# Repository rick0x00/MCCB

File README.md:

# MCCB
MODULO DE CONTROLE DE CARRINHO DE BRINQUEDO

## Warning
I, the project maintainer ,am a beginner in this Open Source world, Git, GitHub... So I apologize in advance for any problems.

## License
At the present time this project is completely under [Apache 2.0 license](http://www.apache.org/licenses/LICENSE-2.0). All Softwares, All Electronic Designs(Schematics), All Documentation and All 3D Design.

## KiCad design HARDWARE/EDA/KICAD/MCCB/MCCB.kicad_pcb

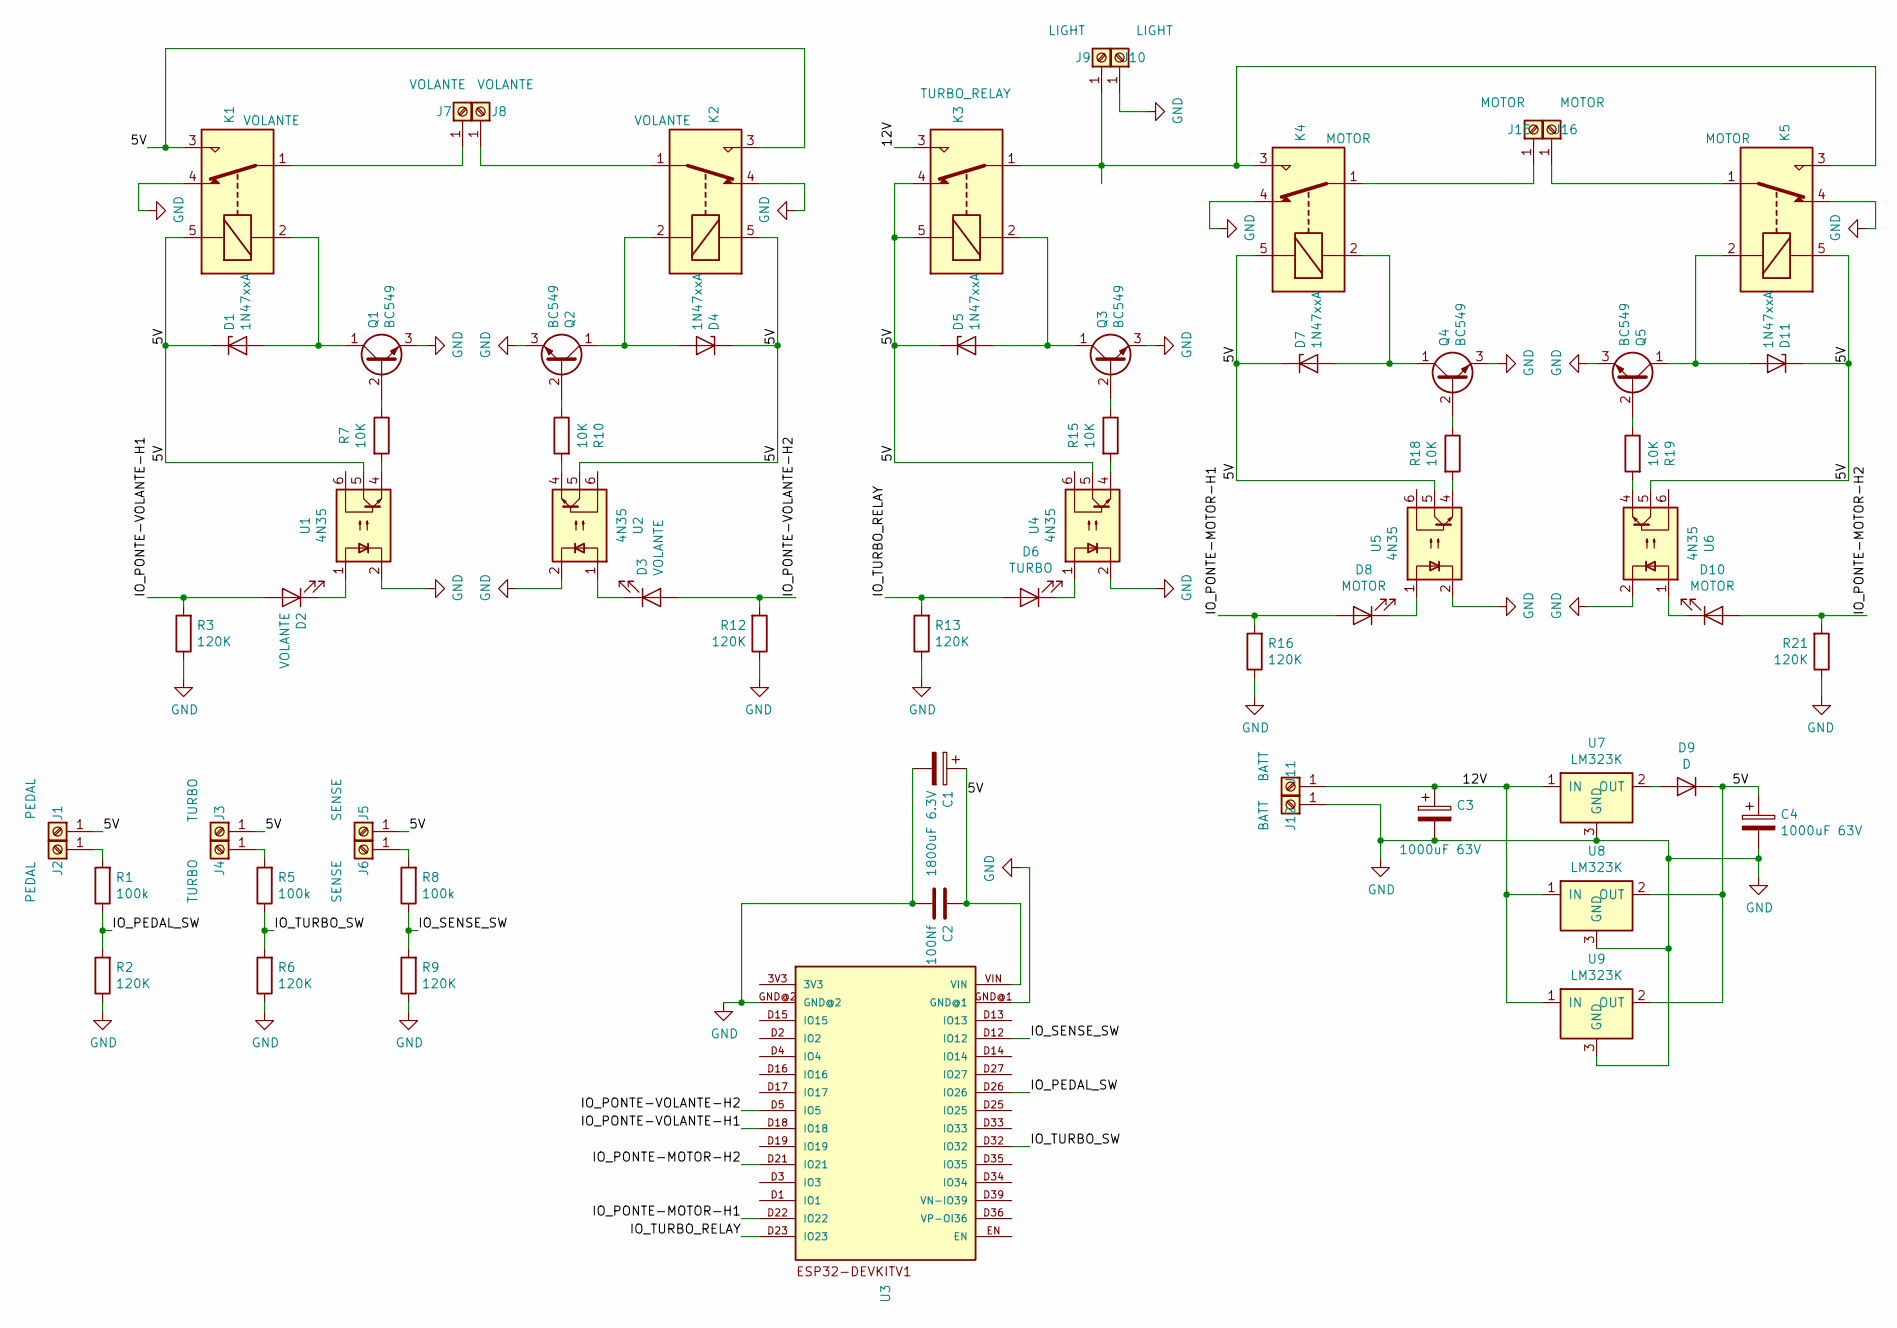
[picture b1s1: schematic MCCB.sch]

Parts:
C1: 1800uF 6.3V; CP_Radial_D10.0mm_P5.00mm
C2: 100Nf; C_Rect_L7.0mm_W2.5mm_P5.00mm
C3, C4: 1000uF 63V; CP_Radial_D16.0mm_P7.50mm
D1, D4, D5, D7, D11: 1N47xxA; D_DO-41_SOD81_P2.54mm_Vertical_AnodeUp
D2, D3: VOLANTE; LED_D5.0mm
D6: TURBO; LED_D5.0mm
D8, D10: MOTOR; LED_D5.0mm
D9: D; D_5KPW_P7.62mm_Vertical_KathodeUp
J1, J2: PEDAL; PinHeader_1x01_P1.00mm_Vertical
J3, J4: TURBO; PinHeader_1x01_P1.00mm_Vertical
J5, J6: SENSE; PinHeader_1x01_P1.00mm_Vertical
J7, J8: VOLANTE; TestPoint_Keystone_5005-5009_Compact
J9, J10: LIGHT; TestPoint_Keystone_5005-5009_Compact
J11, J12: BATT; TestPoint_Keystone_5005-5009_Compact
J15, J16: MOTOR; TestPoint_Keystone_5005-5009_Compact
K1, K2: VOLANTE; Relay_SPDT_Omron-G5LE-1
K3: TURBO_RELAY; Relay_SPDT_Omron-G5LE-1
K4, K5: MOTOR; Relay_SPDT_Omron-G5LE-1
Q1, Q2, Q3, Q4, Q5: BC549; TO-92_Inline
R1, R5, R8: 100k; R_Axial_DIN0204_L3.6mm_D1.6mm_P1.90mm_Vertical
R2, R3, R6, R9, R12, R13, R16, R21: 120K; R_Axial_DIN0204_L3.6mm_D1.6mm_P1.90mm_Vertical
R7, R10, R15, R18, R19: 10K; R_Axial_DIN0204_L3.6mm_D1.6mm_P1.90mm_Vertical
U1, U2, U4, U5, U6: 4N35; DIP-6_W7.62mm
U3: ESP32DEVKITV1; ESP32-DEVKITV1
U7, U8, U9: LM323K; TO-3

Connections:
/5V: C1.1, C2.1, C4.1, D1.1 (K), D4.1 (K), D5.1 (K), D7.1 (K), D9.1 (K), D11.1 (K), J1.1, J3.1, J5.1, K1.3, K1.5, K2.3, K2.5, K3.4, K3.5, K4.5, K5.5, U1.5, U2.5, U3.VIN, U4.5, U5.5, U6.5, U8.2 (OUT), U9.2 (OUT)
/12V: C3.1, J11.1, K3.3, U7.1 (IN), U8.1 (IN), U9.1 (IN)
/IO_PEDAL_SW: R1.1, R2.2, U3.D26 (IO26)
/IO_PONTE-MOTOR-H1: D8.2 (A), R16.2, U3.D22 (IO22)
/IO_PONTE-MOTOR-H2: D10.2 (A), R21.2, U3.D21 (IO21)
/IO_PONTE-VOLANTE-H1: D2.2 (A), R3.2, U3.D18 (IO18)
/IO_PONTE-VOLANTE-H2: D3.2 (A), R12.2, U3.D5 (IO5)
/IO_SENSE_SW: R8.1, R9.2, U3.D12 (IO12)
/IO_TURBO_RELAY: D6.2 (A), R13.2, U3.D23 (IO23)
/IO_TURBO_SW: R5.1, R6.2, U3.D32 (IO32)
GND: C1.2, C2.2, C3.2, C4.2, J10.1, J12.1, K1.4, K2.4, K4.4, K5.4, Q1.3 (E), Q2.3 (E), Q3.3 (E), Q4.3 (E), Q5.3 (E), R2.1, R3.1, R6.1, R9.1, R12.1, R13.1, R16.1, R21.1, U1.2, U2.2, U3.GND@1, U3.GND@2, U4.2, U5.2, U6.2, U7.3 (GND), U8.3 (GND), U9.3 (GND)
unnamed: D1.2 (A), K1.2, Q1.1 (C)
unnamed: D2.1 (K), U1.1
unnamed: D3.1 (K), U2.1
unnamed: D4.2 (A), K2.2, Q2.1 (C)
unnamed: D5.2 (A), K3.2, Q3.1 (C)
unnamed: D6.1 (K), U4.1
unnamed: D7.2 (A), K4.2, Q4.1 (C)
unnamed: D8.1 (K), U5.1
unnamed: D9.2 (A), U7.2 (OUT)
unnamed: D10.1 (K), U6.1
unnamed: D11.2 (A), K5.2, Q5.1 (C)
unnamed: J2.1, R1.2
unnamed: J4.1, R5.2
unnamed: J6.1, R8.2
unnamed: J7.1, K1.1
unnamed: J8.1, K2.1
unnamed: J9.1, K3.1, K4.3, K5.3
unnamed: J15.1, K4.1
unnamed: J16.1, K5.1
unnamed: Q1.2 (B), R7.1
unnamed: Q2.2 (B), R10.1
unnamed: Q3.2 (B), R15.1
unnamed: Q4.2 (B), R18.1
unnamed: Q5.2 (B), R19.1
unnamed: R7.2, U1.4
unnamed: R10.2, U2.4
unnamed: R15.2, U4.4
unnamed: R18.2, U5.4
unnamed: R19.2, U6.4

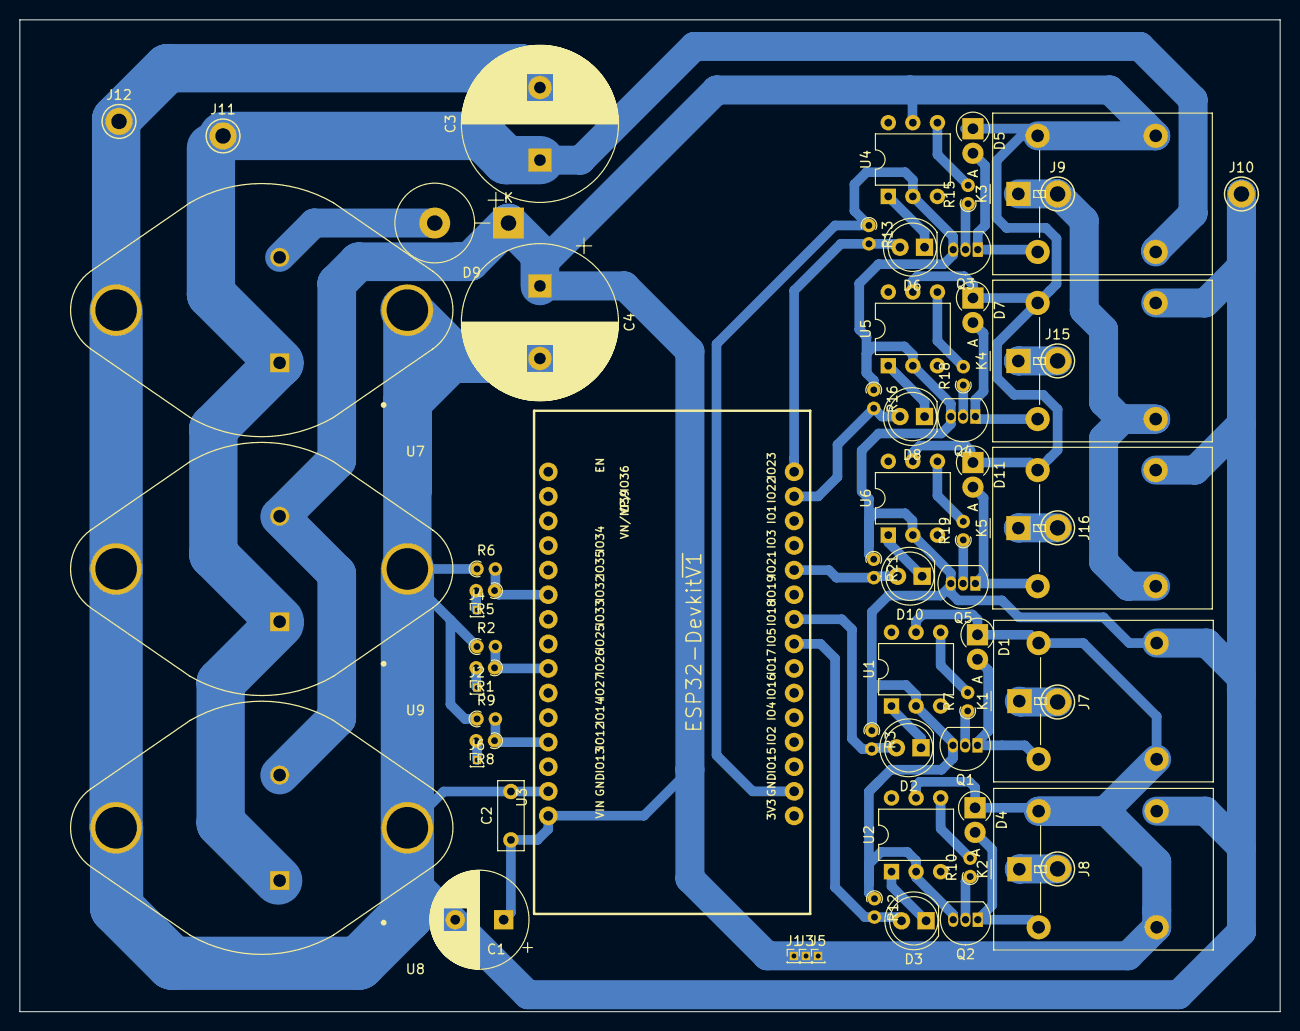
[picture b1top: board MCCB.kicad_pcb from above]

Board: 2 copper layers, 130.2 x 102.5 mm, 64 parts (0 on the bottom side), 40 nets.

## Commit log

2021-09-07 Upload Files
2021-09-09 Udate files and export images
2021-09-13 add value 0 before code
2021-09-13 code adjust
2021-09-13 adjusts
2021-09-15 adjust
